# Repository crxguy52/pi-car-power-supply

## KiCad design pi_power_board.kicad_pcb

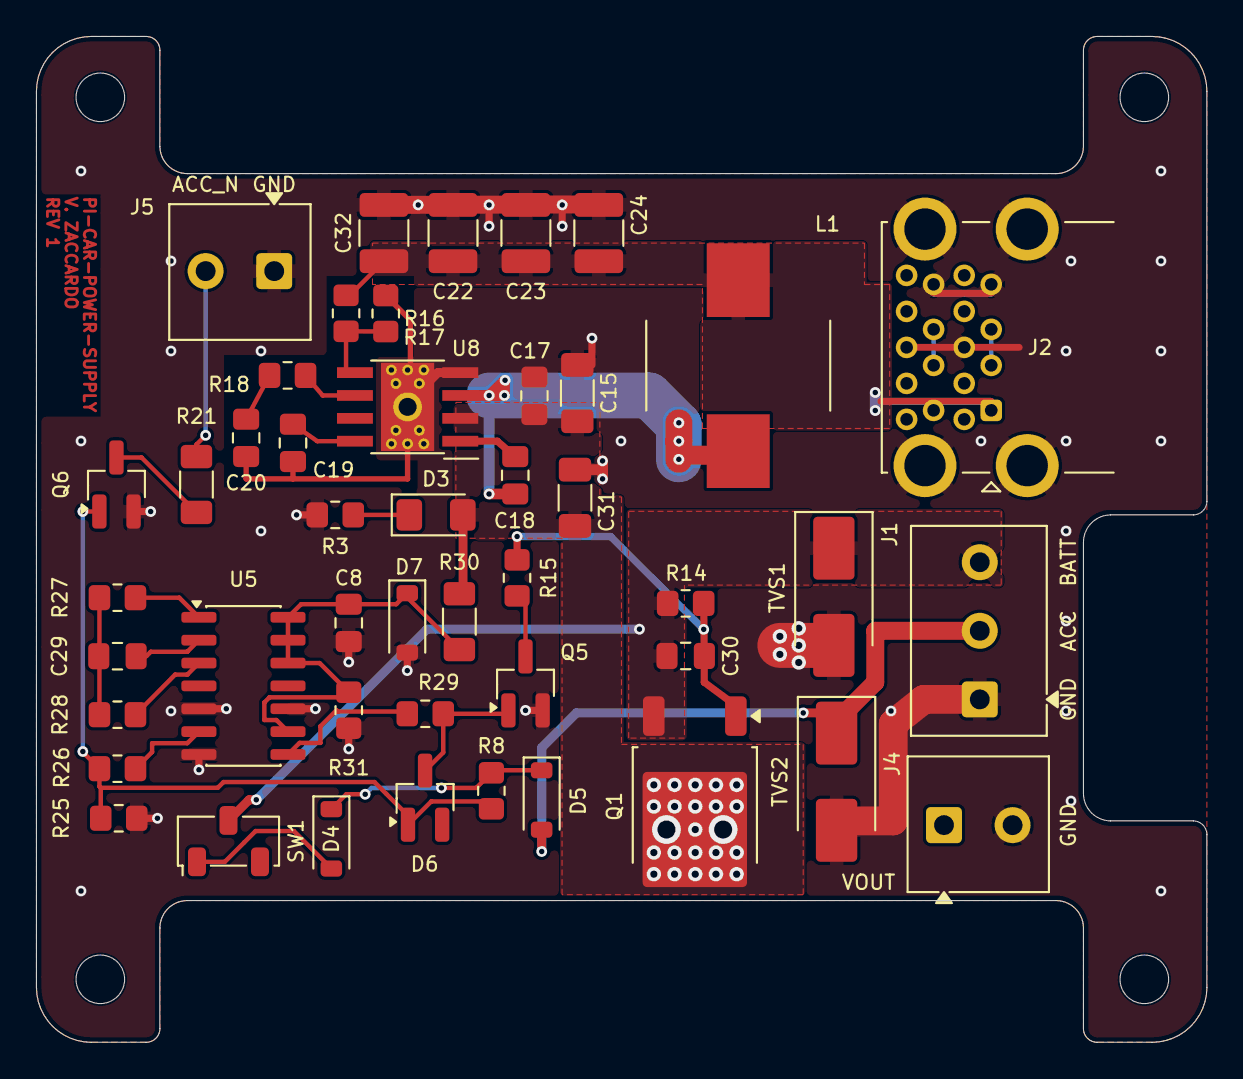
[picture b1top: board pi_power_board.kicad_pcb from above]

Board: 2 copper layers, 65.0 x 55.9 mm, 50 parts (0 on the bottom side), 29 nets.

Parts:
C8: 1 µF 50 V; C_0805_2012Metric_Pad1.18x1.45mm_HandSolder
C15, C31: 10 µF 50 V; C_1206_3216Metric_Pad1.33x1.80mm_HandSolder
C17, C18, C30: 100 nF 50 V; C_0805_2012Metric_Pad1.18x1.45mm_HandSolder
C19: 10 nF 50 V; C_0805_2012Metric_Pad1.18x1.45mm_HandSolder
C20: 15 nF 50 V; C_0805_2012Metric_Pad1.18x1.45mm_HandSolder
C22, C23, C24, C32: 47 µF 10 V X7R; C_1210_3225Metric_Pad1.33x2.70mm_HandSolder
C29: 10 nF 50 V C0G ±1 %; C_0805_2012Metric_Pad1.18x1.45mm_HandSolder
D3: VFR1105W; LED_1206_3216Metric_Pad1.42x1.75mm_HandSolder
D4, D5: 1N4148W; D_SOD-123
D6: BAS116LT1G; SOT-23_Handsoldering
D7: BZT52C5V1; D_SOD-123
J1: Screw terminal 3-pos; TerminalBlock_Phoenix_MKDS-1-3-3.81_1x03_P3.81mm_Horizontal
J2: USB3_A_Stacked; USB3_A_Molex_48406-0001_Horizontal_Stacked
J4: Screw terminal 2-pos; TerminalBlock_Phoenix_MKDS-1-2-3.81_1x02_P3.81mm_Horizontal
J5: ACC_N GND; TerminalBlock_Phoenix_MKDS-1-2-3.81_1x02_P3.81mm_Horizontal
L1: SRP1038A-150M; L_Bourns_SRP1038A
MH1, MH2, MH3, MH4: MountingHole_2.7mm_M2.5
Q1: SQD50P04-13L; TO-252-2
Q5, Q6: 2N7002BK; SOT-23_Handsoldering
R3: 5.1 kΩ; R_0805_2012Metric_Pad1.20x1.40mm_HandSolder
R8: 22 kΩ 1 %; R_0805_2012Metric_Pad1.20x1.40mm_HandSolder
R14: 220 kΩ 1 %; R_0805_2012Metric_Pad1.20x1.40mm_HandSolder
R15: 180 kΩ 1 %; R_0805_2012Metric_Pad1.20x1.40mm_HandSolder
R16: 73.2 kΩ 1 %; R_0805_2012Metric_Pad1.20x1.40mm_HandSolder
R17: 13.7 kΩ 1 %; R_0805_2012Metric_Pad1.20x1.40mm_HandSolder
R18: 7.32 kΩ 1 %; R_0805_2012Metric_Pad1.20x1.40mm_HandSolder
R21: 1.5 kΩ; R_1206_3216Metric_Pad1.30x1.75mm_HandSolder
R25: 27 kΩ 1 %; R_0805_2012Metric_Pad1.20x1.40mm_HandSolder
R26: 100 kΩ; R_0805_2012Metric_Pad1.20x1.40mm_HandSolder
R27: 39.2 kΩ 1 %; R_0805_2012Metric_Pad1.20x1.40mm_HandSolder
R28: 78.7 kΩ 1 %; R_0805_2012Metric_Pad1.20x1.40mm_HandSolder
R29: 47 kΩ; R_0805_2012Metric_Pad1.20x1.40mm_HandSolder
R30: 1.3 kΩ 1 %; R_1206_3216Metric_Pad1.30x1.75mm_HandSolder
R31: 10 kΩ 1 %; R_0805_2012Metric_Pad1.20x1.40mm_HandSolder
SW1: SW_Nidec_CAS-120A1; Nidec_Copal_CAS-120A
TVS1, TVS2: SMBJ16A; D_SMB_Handsoldering
U5: CD4541BM96; SOIC-14_3.9x8.7mm_P1.27mm
U8: TPS54336ADDA; TI_DDA_PowerPAD-8_HandSolder

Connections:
/+5V1: C22.1, C23.1, C24.1, C32.1, J2.1, J2.10, L1.2, R16.1
/ACC_G: D6.1, Q6.1, R8.2, R25.1, R26.1
/ACC_IN: D5.2, J1.2, TVS2.1
/ACC_N: J5.2, R21.2
/ACC_S: D4.1, D5.1, R8.1
/BATT: C30.1, J1.3, Q1.3, R14.1, SW1.2, TVS1.1
/D3_K: D3.1, R3.1
/DRV: Q5.3, R15.2
/HOLD_G: D6.3, Q5.1, R29.2
/Q1_G: C30.2, Q1.1, R14.2, R15.1
/STAT_O: Q6.3, R21.1
/SW1_C: D4.2, SW1.1
/U5_CTC: C29.1, U5.2
/U5_MR: R26.2, U5.6
/U5_OUT: R29.1, U5.8
/U5_RS: R28.1, U5.3
/U5_RTC: R27.1, U5.1
/U5_TJ: C29.2, R27.2, R28.2
/U8_BOOT: C18.1, U8.1
/U8_COMP: R18.1, U8.6
/U8_CRC: C20.1, R18.2
/U8_FB: R16.2, R17.1, U8.5
/U8_PH: C18.2, L1.1, U8.3
/U8_SS: C19.1, U8.8
/USB1_D: J2.2, J2.3
/USB2_D: J2.11, J2.12
/VDD_TMR: C8.1, D7.1, R30.2, R31.1, U5.9, U5.12, U5.13, U5.14
/VOUT: C15.1, C17.1, C31.1, D3.2, J4.1, Q1.2, R30.1, U8.2
GND: C8.2, C15.2, C17.2, C19.2, C20.2, C22.2, C23.2, C24.2, C31.2, C32.2, D7.2, J1.1, J2.4, J2.7, J2.13, J2.16, J2.SH, J4.2, J5.1, Q5.2, Q6.2, R3.2, R17.2, R25.2, R31.2, TVS1.2, TVS2.2, U5.5, U5.7, U5.10, U8.4, U8.9

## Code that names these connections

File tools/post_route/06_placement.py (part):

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- prints the courtyard-gap statistics (per part: the smallest gap to any other courtyard).

Plan (y down; SLVSCD5D 10.1, SPEC 5):
- power corner (inside the J1 BATT -> Q1 -> VOUT -> J4 loop): Q1 (TO-252, pins up, tab down) in the J4 corner,
  so the VOUT tab feeds J4 pin 1 over a short strip (CHANNELS 'VOUT strip'); BATT runs from J1 pin 3 left along
  the top of the corner and down into Q1 S ('BATT run'); C30 straddles G-S just above the pins, R14 above it,
  both with pin 1 on the BATT down-segment; TVS1 beside them with its cathode in the BATT run, anode to GND next
  to the J1 GND pin; Q1 tab gets the corner copper (SPEC 5: >= 1 in2 VOUT where it fits);
- buck along the top (TI layout guide, mirrored onto the J2 side): U8 power pins (GND, PH, VIN, BOOT) to the
  right; C17 (100 nF) then C15 (10 uF) at VIN/GND, VIN rail below them, GND rail above; PH through vias under
  C17 to C18 (BOOT) and L1 pin 1 (small PH area, TI: SW pour on the bottom); L1 below the output caps; C22-C24
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- VOUT to the buck: one up-run from the Q1 tab, left of the BATT down-segment, between C18 and L1 into the VIN
  rail at C15 ('VOUT up-run');
- timer (SPEC 5 "Timer layout"): U5 left of centre; R27 / C29 / R28 in a column at the oscillator pins 1-3, their
  common U5_TJ pins in a line (short TJ / RS node, far from PH and L1); C8 at pin 14 with D7 and R31 next to it,
  R30 between them and the VOUT up-run; R26 at MR (pin 6);
- gate drive and HOLD_G: Q5, R15, R29, D6 between U5 and the VOUT up-run (Q5 near the Q1 gate network; Q1_G
  reaches R15 through a short bottom jumper under the BATT down-segment: routing phase);
- ACC input: TVS2, D5, R8, R25 at the lower right of the logic area, the closest spot outside the power loop
  to J1 (ACC_IN leaves J1 pin 2 on the bottom layer: routing phase); D4 by SW1;
- status: Q6 and R21 next to J5 (R21 at the ACC_N pin);
- SW1 at the left board edge (the free edge: J2/J1/J4 on the right, GPIO header on top, Waveshare IO at the
  bottom), slide parallel to the edge, top actuated; D3 (VOUT LED) and R3 next to it, visible from above.
- routing channels: power copper on top (BATT, VOUT >= 3 mm), bottom = GND pour (routing phase).
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    # ACC input (TVS2 first: the largest): TVS2 cathode at the bottom next to D5's anode
    ('TVS2', 155.0, 101.3, 90, False), ('D5', 151.0, 101.5, 270, False), ('R8', 147.3, 99.3, 180, True),
    ('R25', 147.3, 102.5, 0, True),
    # HOLD_G: D6 and R29 between U5 OUT (pin 8) and Q5's gate
    ('R29', 148.6, 96.3, 0, True),
]

# board-level pin names (text, x, y, angle deg) mm, after 05's pin order: J1 and J5 in front of the wire entry;
# J4 beside its pins (its wire face is 0.6 mm from the Waveshare-notch edge: no room in front)
PIN_LABELS = [('BATT', 184.4, 87.63, 90.0), ('ACC', 184.4, 91.44, 90.0), ('GND', 184.4, 95.25, 90.0),
              ('12V', 174.3, 102.235, 90.0), ('GND', 184.4, 102.235, 90.0),
              ('ACC_N', 138.938, 66.6, 0.0), ('GND', 142.748, 66.6, 0.0)]
OLD_LABEL_TEXTS = {'GND', 'ACC', 'BATT', '12V', 'ACC_N'}     # 02's labels (old pin order)
LABEL_SIZE_MM = 0.8
LABEL_THICK_MM = 0.12
REF_SIZE_MM = 0.8
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
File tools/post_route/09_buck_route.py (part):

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     the GND pour (assumption: the pour under U8 is the single join point; fig. 55's separate analog ground trace
     is not drawn).
3. Power paths, as locked zones (filled by this script) and tracks:
   - `BATT` top: J1 pin 3 -> TVS1 -> along the J2 / L1 side -> down to Q1's source pin, with R14 / C30's `BATT`
     pads in the pour (>= 3.1 mm wide);
   - `VOUT`: Q1 tab top pour (as large as TVS2 and the Q1 pins allow) -> 23 vias -> bottom pour from the tab to J4
     pin 1 (TVS2 sits between the tab and J4 on top); the top `VOUT` run from the tab past the `BATT` feed up to the
     buck input (C15 / C17 / U8 pin 2), with D3 / R30 tapped off it;
   - `+5V1`: L1 pad 2 and C22-C24 in one top pour to the J2 VBUS pins (necks above);
   - `ACC_IN`: J1 pin 2 -> TVS2 pad first (top, 1.0 mm), then via the bottom to D5 (no branch before TVS2:
     placement review); TVS2's GND pad on top to J1's GND pin; TVS1's GND pad to the bottom GND by 5 vias;
   - `Q1_G` on top from Q1 pin 1 to C30 and R14, and R15's jumper on the bottom under the `VOUT` run and the
     `BATT` pour (both on top there);
   - a `BATT` via in the `BATT` pour (BATT_FEED_VIA): SW1's feed (signal current) is routed from it by 10.
4. Q1 tab hand-solder provisions (project lead): in the tab pad, 2 solder-feed vias (1.0 mm drill) and 21 thermal
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    (PH, F, [PH_BOOT_VIA, (151.0, 73.9)], W_PH_BOOT),
    ('/U8_BOOT', F, [(152.35, 71.7), (152.35, 76.2), (151.3, 76.2)], W_BOOT),
    # hot loop and GND bus
    (VOUT, F, [(152.5, 70.43), (154.9, 70.43)], W_PIN),
    (VOUT, F, [(155.4, 70.5), (158.2, 70.8)], W_CIN),
    (GND, F, [(152.5, 67.89), (150.6, 67.89), (149.9, 68.6)], W_PAD_LINK),
    (GND, F, [(152.5, 67.89), (154.9, 67.89)], W_PIN),
    (GND, F, [(155.4, 67.75), (169.92, 67.75)], W_BUS),
    # SS, COMP, CRC, FB, VOUT sense
    ('/U8_SS', F, [(145.5, 71.7), (145.6, 73.9)], W_SS),
    ('/U8_COMP', F, [COMP_VIA_PIN, (145.4, 69.16)], W_SS),
    ('/U8_COMP', B, [COMP_VIA_PIN, (144.6, 73.4), COMP_VIA_R18], W_SIG),
    ('/U8_CRC', F, [(148.0, 76.5), (147.55, 77.3), (147.55, 81.6), (148.6, 81.6)], W_SIG),
    ('/U8_FB', F, [(145.4, 67.89), (143.6, 67.89), (143.6, 81.49), (142.4, 81.49)], W_SIG),
    ('/U8_FB', F, [(143.6, 81.49), (145.6, 81.49)], W_SIG),
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    (P5, F, [(173.9, VBUS_Y), (J2_PIN1_X, VBUS_Y)], W_NECK),
    (P5, B, [VBUS_VIAS[0], VBUS_VIAS[1]], W_VBUS_VIA),
    (P5, B, [(VBUS_VIAS[0][0], VBUS_Y), (J2_PIN1_X, VBUS_Y)], W_NECK),
    # ACC_IN: J1 pin 2 -> TVS2 -> bottom -> D5
    ('/ACC_IN', F, [(179.41, 91.44), (173.6, 91.44), (173.6, 94.3), (171.9, 96.0)], W_ACC),
    ('/ACC_IN', F, [(171.0, 96.0), ACC_VIA_TVS2], W_ACC_RUN),
    ('/ACC_IN', B, [ACC_VIA_TVS2, (157.0, 96.0), (155.07, 97.93), ACC_VIA_D5], W_ACC_RUN),
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VIAS = [  # (net, xy, (dia, drill))
    (PH, PH_A, VIA_SIG), (PH, PH_B, VIA_SIG), (PH, PH_BOOT_VIA, VIA_SIG),
    *[(PH, v, VIA_SIG) for v in PH_L1_VIAS],
    ('/U8_COMP', COMP_VIA_PIN, VIA_SIG), ('/U8_COMP', COMP_VIA_R18, VIA_SIG),
    *[(GND, v, VIA_SIG) for v in BUS_VIAS],
    *[(P5, v, VIA_SIG) for v in VBUS_VIAS],
    ('/ACC_IN', ACC_VIA_TVS2, VIA_SIG), ('/ACC_IN', ACC_VIA_D5, VIA_SIG), (BATT, BATT_FEED_VIA, VIA_SIG),
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
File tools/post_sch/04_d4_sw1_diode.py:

"""Post-schematic edit 04 (2026-11-05, schematic staff review): restore D4 in series with SW1; sheet title.

Run from the project root with the PDM python (KiCad must not have the schematic open):

    pdm run python -I tools/post_sch/04_d4_sw1_diode.py [--dry-run]

What and why (SPEC 2 "ACC sense", SPEC 6 Parts "D4, D5", SPEC 7 rows SW1 and D4; DECISIONS 2026-11-05 "D4
restored"): 03 tied SW1 pin 1 straight to `ACC_S` on the reasoning that SW1 only ever connects `BATT` to `ACC_S`.
That holds only while `BATT` is alive. With SW1 closed and `BATT` dead (harness fuse blown, or a bench supply on ACC
only) the ACC line feeds `BATT` backwards through D5 and SW1, and Q1 (held on by the charged C5) passes the whole
load: D5 is a 1N4148W (continuous I_F 300 mA, Vishay datasheet) and SW1 is rated 100 mA non-switching (Nidec CAS
catalogue), against a 3.5-5 A load. D4 (1N4148W, the D5 part) between SW1 pin 1 (`SW1_C`) and `ACC_S` blocks that
path; in SW1 mode `ACC_S` becomes `BATT` minus one diode drop, the same as a key-on through D5.

- D4 is added with the 03 layout engine (03's PARTS / LINKS plus one part and one link, same uuid5 namespace), so
  every other item of the sheet keeps its bytes; the only removed items are SW1 pin 1's stub and its `ACC_S` label.
- Title block: title only (the sheet had none).

Guards: refuses if KiCad's lock file exists. Accepts two states: (1) pre-edit: the sheet is byte-identical to what
03 wrote (SHA-256 below); (2) applied: the sheet equals what this script writes ("already applied"). Anything else
stops. Before writing, it runs 03's own checks (grid, wires, connectivity vs SPEC 7, overlaps, A4 frame) and checks
that the change set is exactly the expected one. Backup to pi_power_board-backups/ before writing; CRLF kept.
"""
import datetime
import hashlib
import importlib.util
import pathlib
import shutil
import sys

TOOLS = pathlib.Path(__file__).resolve().parent.parent
sys.path.insert(0, str(TOOLS))
import check_netlist  # noqa: E402
import sexpr  # noqa: E402

S03_PATH = TOOLS / 'post_sch' / '03_simplified.py'
_spec = importlib.util.spec_from_file_location('post_sch_03', S03_PATH)
s03 = importlib.util.module_from_spec(_spec)
_spec.loader.exec_module(s03)

SHEET, LOCK, BACKUPS, ROOT, STEM = s03.SHEET, s03.LOCK, s03.BACKUPS, s03.ROOT, s03.STEM
PRE_SHA256 = '165005d233b49a8250f16413d221ae68eb2472a1d401c6dd588dcd166baaa593'   # the sheet as 03 wrote it
NEW_REF = 'D4'
NEW_PINS = {'1': 'ACC_S', '2': 'SW1_C'}
SW1_PIN1_NET = 'SW1_C'
D4_PLACE = ('D4', 'D', 54, 64, 180)              # ref, kind, x, y (grid units), rotation: anode left, as D5
D4_FIELDS = 'below'
D4_LINK = ('SW1_C', ['SW1.1', 'D4.2'], (35, 64), 0)
TITLE = 'Pi 5 car power HAT'
PAPER_LINE = f'(paper {s03.PAPER_NEW})'
# Items of the 03 sheet that 04 replaces: SW1 pin 1 stub wire and its ACC_S label
EXPECTED_REMOVED_KINDS = {'wire': 1, 'label': 1}
EXPECTED_ADDED_KINDS = {'symbol': 1, 'wire': 3, 'label': 2}   # link split at its label + D4 cathode stub


def sha256(text):
    return hashlib.sha256(text.encode('utf-8')).hexdigest()


def build(src, spec, parts_table, layout):
    """Sheet text from 03's engine with the given PARTS / LINKS (mirrors 03 main)."""
    text = src.replace('\r\n', '\n')
    blocks = s03.top_level_blocks(text)
    old = s03.read_old(text, blocks)
    old_kept = {(r, v['unit']): v for r, vs in old.items() if r in spec for v in vs}
    s03.PARTS[:], s03.LINKS[:] = layout
    sheet = s03.Sheet(spec, parts_table, old_kept)
    sheet.build()
    sheet.check_grid()
    sheet.check_wires()
    sheet.check_connectivity()
    sheet.check_overlaps()
    root_uuid = sexpr.find(sexpr.parse(text[:text.index('(lib_symbols')] + ')'), 'uuid')[1]
    lib_s = next(a for a, b in blocks if text.startswith('(lib_symbols', a))
    si_s, si_e = next((a, b) for a, b in blocks if text.startswith('(sheet_instances', a))
    head = text[:text.rfind('\n', 0, lib_s) + 1]
    body = '\n'.join([sheet.lib_symbols_text()] + sheet.items_text(f'/{root_uuid}'))
    return head + body + '\n\t' + text[si_s:si_e] + text[si_e:]


def with_title(text):
    if '(title_block' in text:
        return text
    if text.count(PAPER_LINE) != 1:
        raise SystemExit(f'{PAPER_LINE} not found once: unexpected state')
    return text.replace(PAPER_LINE, f'{PAPER_LINE}\n\t(title_block\n\t\t(title {s03.q(TITLE)})\n\t)', 1)


def item_blocks(text):
    """{block text: kind} of the placed items (symbols, wires, labels, ...), lib_symbols excluded."""
    out = {}
    for a, b in s03.top_level_blocks(text):
        blk = text[a:b]
        kind = blk[1:blk.find('\n') if '\n' in blk else None].split()[0]
        if kind not in ('lib_symbols', 'sheet_instances', 'title_block', 'paper', 'version', 'generator',
                        'generator_version', 'uuid', 'embedded_fonts'):
            out[blk] = kind
    return out


def check_changes(before, after):
    old, new = item_blocks(before), item_blocks(after)
    removed = [k for b, k in old.items() if b not in new]
    added = [k for b, k in new.items() if b not in old]
    count = lambda kinds: {k: kinds.count(k) for k in sorted(set(kinds))}  # noqa: E731
    if count(removed) != EXPECTED_REMOVED_KINDS or count(added) != EXPECTED_ADDED_KINDS:
        raise SystemExit(f'change set removed {count(removed)}, added {count(added)}; expected '
                         f'{EXPECTED_REMOVED_KINDS} / {EXPECTED_ADDED_KINDS}: stop')
    lib_old = [before[a:b] for a, b in s03.top_level_blocks(before) if before.startswith('(lib_symbols', a)]
    lib_new = [after[a:b] for a, b in s03.top_level_blocks(after) if after.startswith('(lib_symbols', a)]
    if lib_old != lib_new:
        raise SystemExit('lib_symbols changed (D4 uses the D5 symbol, already embedded): stop')
    return count(removed), count(added)


def main(argv):
    dry = '--dry-run' in argv
    if LOCK.exists():
        raise SystemExit(f'{LOCK.name} exists: close the schematic in KiCad first')
    md = check_netlist.SPEC.read_text(encoding='utf-8')
    spec, parts_table = check_netlist.parse_netlist_table(md), check_netlist.parse_parts_table(md)
    want = set(s03.SURVIVING) | set(s03.NEW) | {NEW_REF}
    if set(spec) != want or spec[NEW_REF]['pins'] != NEW_PINS or spec['SW1']['pins'].get('1') != SW1_PIN1_NET:
        raise SystemExit('SPEC 7 is not the D4 state this script implements (refs, D4 pins, SW1 pin 1): stop')
    with open(SHEET, encoding='utf-8', newline='') as fh:
        src = fh.read()
    eol = '\r\n' if '\r\n' in src else '\n'
    text = src.replace('\r\n', '\n')

    layout = (list(s03.PARTS) + [s03.P(*D4_PLACE, fields=D4_FIELDS)], list(s03.LINKS) + [D4_LINK])
    pre_edit = sha256(src) == PRE_SHA256
    out = with_title(build(text, spec, parts_table, layout))
    if not pre_edit:
        if out.replace('\n', eol) == src:
            print(f'{SHEET.name}: already applied (D4 in series with SW1); nothing changed')
            return
        raise SystemExit(f'{SHEET.name}: neither the 03 sheet (SHA-256 {PRE_SHA256[:12]}...) nor the 04 result: '
                         'stop; edit by hand or with a new script')
    removed, added = check_changes(text, out)
    if dry:
        print(f'dry run: checks passed; would remove {removed}, add {added}; nothing written')
        return
    stamp = datetime.datetime.now().strftime('%Y-%m-%d_%H%M%S')
    BACKUPS.mkdir(exist_ok=True)
    backup = BACKUPS / f'{STEM}_{stamp}.kicad_sch'
    shutil.copy2(SHEET, backup)
    with open(SHEET, 'w', encoding='utf-8', newline='') as fh:
        fh.write(out.replace('\n', eol))
    print(f'backup {backup.relative_to(ROOT)}')
    print(f'{SHEET.name}: D4 added (SW1_C -> ACC_S); removed {removed}, added {added}; title "{TITLE}"')


if __name__ == '__main__':
    main(sys.argv)

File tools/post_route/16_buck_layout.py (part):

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- Power block: U8, C17, C15 and their local copper (PH vias and stubs, VIN / GND links, the C15 GND fan-out via)
  moved as one rigid block by BLOCK_MOVE, from the top edge to below J5. The hot loop geometry (fig. 55) is
  unchanged; the left side of U8 is now free of J5.
- FB: R16 / R17 above U8 pin 5 (U8_FB node 5.5 mm of trace, was 18.6 mm); the +5V1 sense line from C24 along the top
  edge now ends at R16 pin 1 (the long run is the low-impedance VOUT sense, 10.1).
- COMP / SS: R18 at pin 6, C20 below it, C19 at pin 8, all F.Cu on the side away from U8_PH (COMP ran on B.Cu
  1.37 mm from PH).
- Analog ground (10.1): R17, C19 and C20 return by separate F.Cu traces to the PowerPAD (R17 at the top end of pad 9,
  C19 + C20 joined at its bottom end: two landing points on the one pad, no loop); rule area AGND_KEEPOUT (F.Cu, no zone fill only) keeps the GND pour off them.
- C18 below C17 (BOOT from pin 1; PH by a B.Cu branch and a via at its PH pad). C31 below C15 on the VOUT pour, GND by
  two vias. L1 moved right by L1_MOVE (C15 courtyard gap). C32 left of C22 on the Cout GND bus.
- PH: B.Cu 1.5 mm trace from the block's PH via to L1's via row (shorter than before); L1's vias / stubs follow L1.
- Zones: VOUT_TOP re-drawn around the moved block (top edge just below the PH via row, the D3 / C18 / C31 area),
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EP_TOP, EP_BOT = (147.619, 77.0), (147.619, 81.2)        # analog ground ends inside pad 9 (U8 at y 79.0)
ADD_SEGS = [
    ('/+5V1', F, W_SIG, [(144.2, 66.65), (144.2, 72.8)]),                       # sense line to R16 pin 1
    ('/U8_FB', F, W_SIG, [(144.2, 74.8), (144.2, 77.095)]),                     # R16 pin 2 to U8 pin 5
    ('/U8_FB', F, W_SIG, [(144.2, 74.8), (146.75, 72.8)]),                      # R16 pin 2 to R17 pin 1
    ('/U8_COMP', F, W_SIG, [(144.0, 78.365), (142.9, 78.365), (141.95, 77.25)]),
    ('/U8_CRC', F, W_SIG, [(139.95, 77.25), (138.65, 79.6825)]),
    ('/U8_SS', F, W_SIG, [(144.0, 80.905), (142.6, 80.905), (141.25, 79.9625)]),
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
